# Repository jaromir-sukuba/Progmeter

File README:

What happens when you combine crappy multimeter and poor programable calculator? More at http://hackaday.io/project/2475-Progmeter

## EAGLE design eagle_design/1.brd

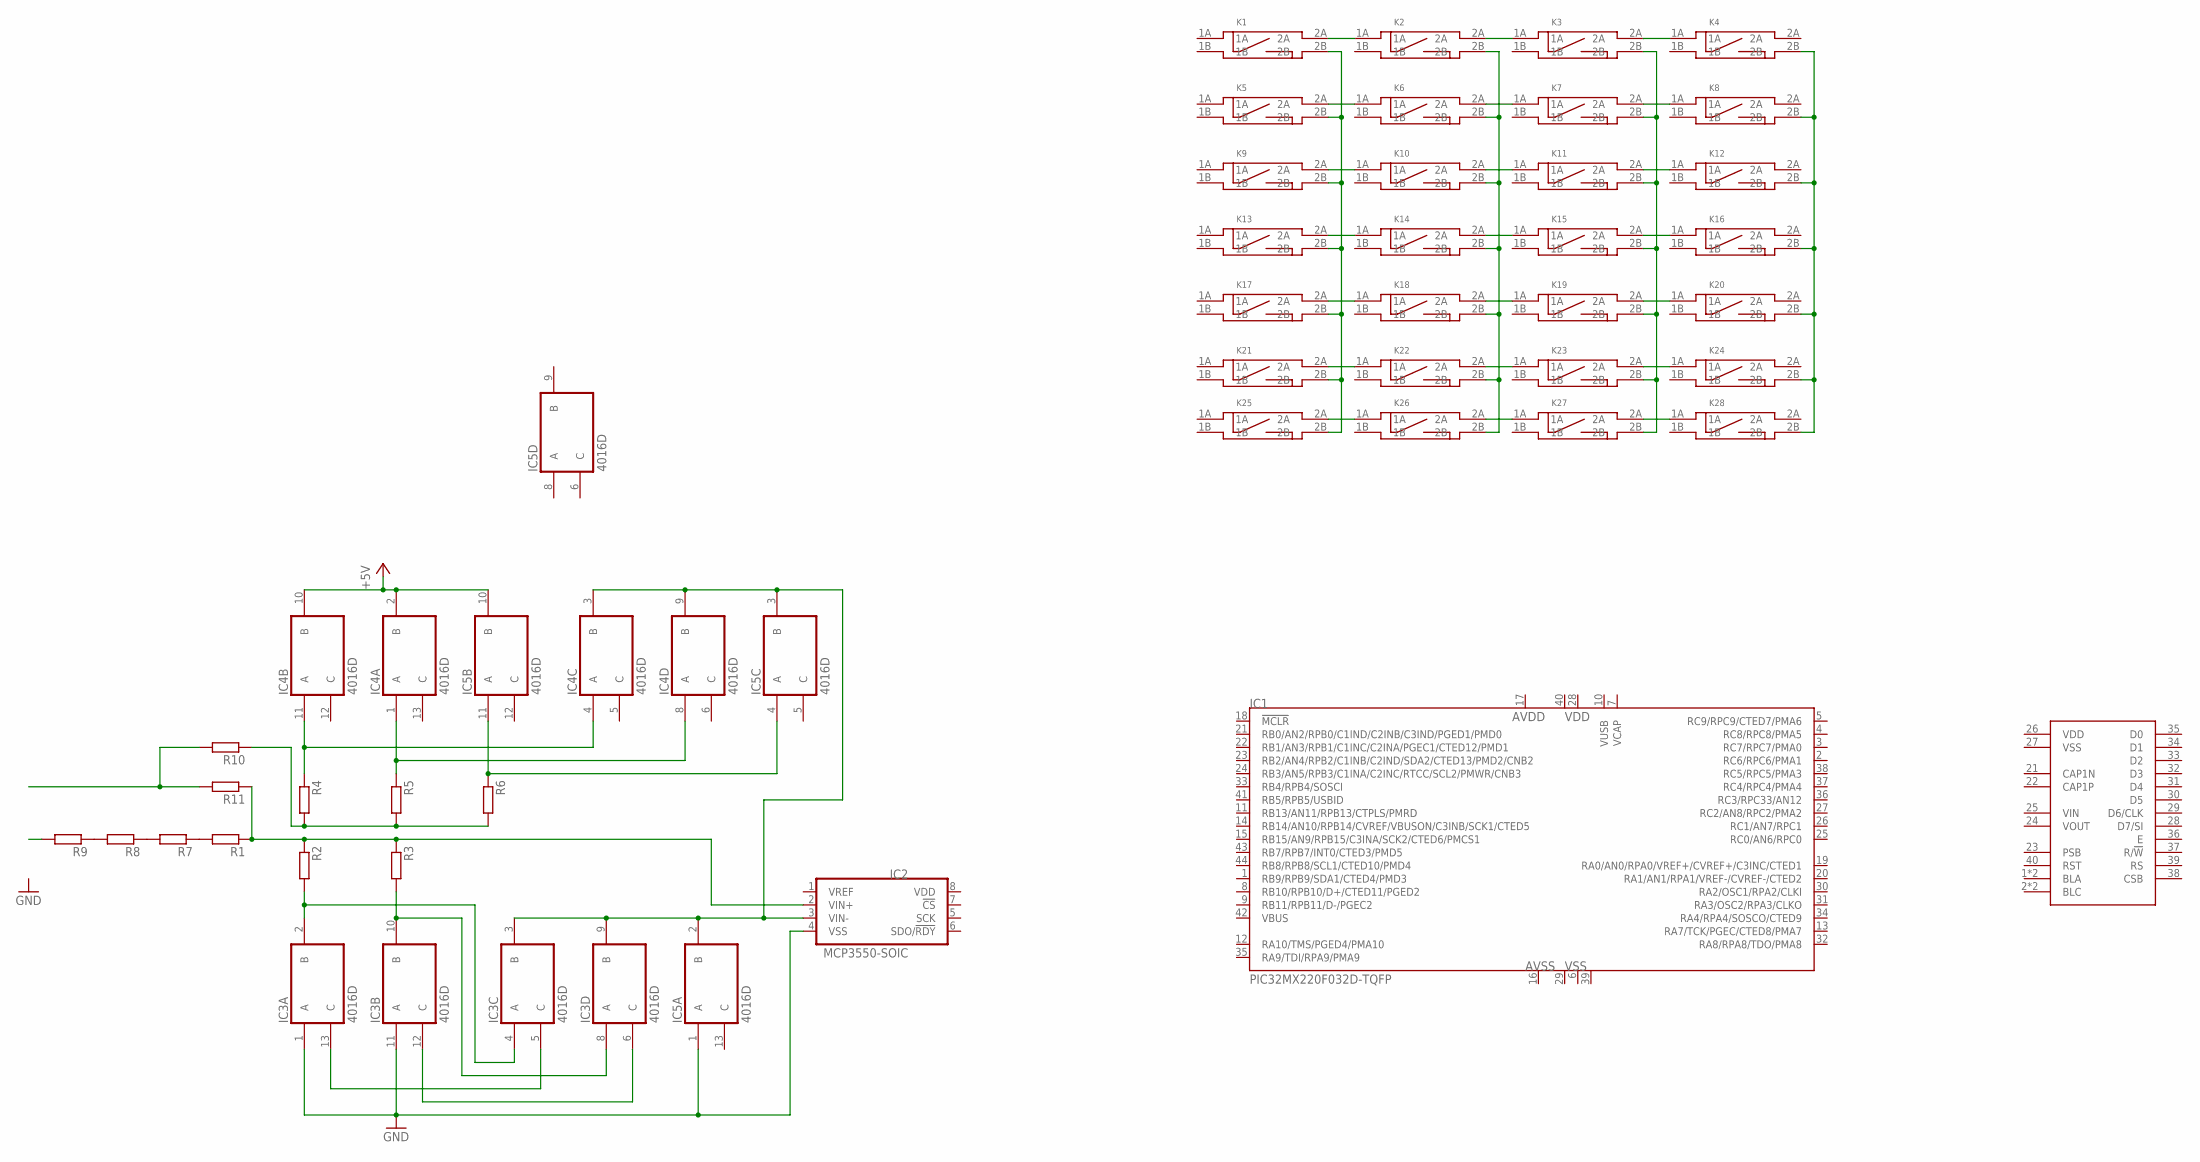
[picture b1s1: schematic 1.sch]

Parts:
IC1: PIC32MX220F032D-TQFP; TQFP44
IC2: MCP3550-SOIC; SO-08
IC3, IC4, IC5: 4016D; SO14
K1, K2, K3, K4, K5, K6, K7, K8, K9, K10, K11, K12, K13, K14, K15, K16, K17, K18, K19, K20, K21, K22, K23, K24, K25, K26, K27, K28: SWITCH_BD_B; SW_SMD2
LCD: EAGOG_M; EADOGM
R1, R2, R3, R4, R5, R6, R7, R8, R9, R10, R11: R_1206; R1206

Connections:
+5V: IC4.2 (B), IC4.10 (B), IC5.10 (B)
AVDD: IC1.17 (AVDD)
AVSS: IC1.16 (AVSS)
GND: IC2.4 (VSS), IC3.1 (A), IC3.11 (A), IC5.1 (A)
unnamed: K25.2A, K26.1A
unnamed: K26.2A, K27.1A
unnamed: K27.2A, K28.1A
unnamed: K21.2A, K22.1A
unnamed: K22.2A, K23.1A
unnamed: K23.2A, K24.1A
unnamed: K19.2A, K20.1A
unnamed: K18.2A, K19.1A
unnamed: K17.2A, K18.1A
unnamed: K13.2A, K14.1A
unnamed: K14.2A, K15.1A
unnamed: K15.2A, K16.1A
unnamed: K11.2A, K12.1A
unnamed: K10.2A, K11.1A
unnamed: K9.2A, K10.1A
unnamed: K5.2A, K6.1A
unnamed: K6.2A, K7.1A
unnamed: K7.2A, K8.1A
unnamed: K1.2A, K2.1A
unnamed: K2.2A, K3.1A
unnamed: K3.2A, K4.1A
unnamed: K1.2B, K5.2B, K9.2B, K13.2B, K17.2B, K21.2B, K25.2B
unnamed: K2.2B, K6.2B, K10.2B, K14.2B, K18.2B, K22.2B, K26.2B
unnamed: K3.2B, K7.2B, K11.2B, K15.2B, K19.2B, K23.2B, K27.2B
unnamed: K4.2B, K8.2B, K12.2B, K16.2B, K20.2B, K24.2B, K28.2B
unnamed: IC3.2 (B), IC3.4 (A), R2.2
unnamed: IC3.8 (A), IC3.10 (B), R3.2
unnamed: IC2.3 (VIN-), IC3.3 (B), IC3.9 (B), IC4.3 (B), IC4.9 (B), IC5.2 (B), IC5.3 (B)
unnamed: R4.2, R5.2, R6.2, R10.1
unnamed: IC4.4 (A), IC4.11 (A), R4.1
unnamed: IC4.1 (A), IC4.8 (A), R5.1
unnamed: R1.2, R7.1
unnamed: IC2.2 (VIN+), R1.1, R2.1, R3.1, R11.1
unnamed: R10.2, R11.2
unnamed: R7.2, R8.1
unnamed: IC5.4 (A), IC5.11 (A), R6.1
unnamed: R8.2, R9.1
unnamed: IC3.5 (C), IC3.13 (C)
unnamed: IC3.6 (C), IC3.12 (C)
VDD: IC1.40 (VDD), IC2.8 (VDD), IC3.14 (VDD), IC4.14 (VDD), IC5.14 (VDD)
VDD2: IC1.28 (VDD2)
VSS: IC1.29 (VSS), IC3.7 (VSS), IC4.7 (VSS), IC5.7 (VSS)
VSS1: IC1.6 (VSS1)
VSS2: IC1.39 (VSS2)

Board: 2 copper layers, 45 parts (1 on the bottom side), 43 nets, no tracks yet.

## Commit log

2014-08-18 ver 1
    -
2014-08-19 eagle v1
    first uncomplete version of eagle files
